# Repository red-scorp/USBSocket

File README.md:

# USBSocket project

USB Socket board came into existence as alternative to cheap miniUSB adapters which we not good enough for me.
These cheap boards do not care about D+/D- traced being equally long which is essential for USB wiring.
I had to design my own microUSB adapter board to fit my needs.

Following types of boards are available:

- **Type1** is breadboard friendly **microUSB** socket
- **Type2** is cable mount friendly **microUSB** socket
- **Type3** is breadboard friendly **miniUSB** socket
- **Type4** is cable mount friendly **miniUSB** socket
- **Type5** is breadboard friendly **USB** socket
- **Type6** is cable mount friendly **USB** socket
- **Type7** is breadboard friendly **PCB-USB** socket
- **Type8** is cable mount friendly **PCB-USB** socket
- **Type9** is breadboard friendly **USB Type-C** socket
- **Type10** is cable mount friendly **USB Type-C** socket

## USBSocket_Type1_v1.0

**USBSocket_Type1_v1.0** is a simple microUSB adapter board, which mostly designed to be breadboard friendly.

Preview:

[Schematics in PDF format](doc/USBSocket_Type1_v1.0.pdf)

Features:

- 2.54mm (0.1") raster breadboard friendly
- small size
- includes decoupling capacitor
- includes power LED indicator
- 3mm mount holes

CAM files are available.

## USBSocket_Type2_v1.0

**USBSocket_Type2_v1.0** is a simple microUSB adapter board mostly usable for smaller or cable applications.

Preview:

[Schematics in PDF format](doc/USBSocket_Type2_v1.0.pdf)

Features:

- 2.54mm (0.1") raster board friendly
- even smaller size
- suitable for cable mount
- shrink-tube friendly

CAM files are available.

## USBSocket_Type3_v1.0

**USBSocket_Type3_v1.0** is a simple miniUSB adapter board, which mostly designed to be breadboard friendly.

Preview:

[Schematics in PDF format](doc/USBSocket_Type3_v1.0.pdf)

Features:

- 2.54mm (0.1") raster breadboard friendly
- small size
- includes decoupling capacitor
- includes power LED indicator
- 3mm mount holes

CAM files are available.

## USBSocket_Type4_v1.0

**USBSocket_Type4_v1.0** is a simple miniUSB adapter board mostly usable for smaller or cable applications.

Preview:

[Schematics in PDF format](doc/USBSocket_Type4_v1.0.pdf)

Features:

- 2.54mm (0.1") raster board friendly
- even smaller size
- suitable for cable mount
- shrink-tube friendly

CAM files are available.

## USBSocket_Type5_v1.0

**USBSocket_Type5_v1.0** is a simple USB adapter board, which mostly designed to be breadboard friendly.

Preview:

[Schematics in PDF format](doc/USBSocket_Type5_v1.0.pdf)

Features:

- 2.54mm (0.1") raster breadboard friendly
- small size
- includes decoupling capacitor
- includes power LED indicator
- 3mm mount holes

CAM files are available.

## USBSocket_Type6_v1.0

**USBSocket_Type6_v1.0** is a simple USB adapter board mostly usable for smaller or cable applications.

Preview:

[Schematics in PDF format](doc/USBSocket_Type6_v1.0.pdf)

Features:

- 2.54mm (0.1") raster board friendly
- even smaller size
- suitable for cable mount
- shrink-tube friendly

CAM files are available.

## USBSocket_Type7_v1.0

**USBSocket_Type7_v1.0** is a simple PCB-USB adapter board, which mostly designed to be breadboard friendly.
This PCB board should be about 1.6-2.0mm thick!

Preview:

[Schematics in PDF format](doc/USBSocket_Type7_v1.0.pdf)

Features:

- 2.54mm (0.1") raster breadboard friendly
- small size
- includes decoupling capacitor
- includes power LED indicator
- 3mm mount holes

CAM files are available.

## USBSocket_Type8_v1.0

**USBSocket_Type8_v1.0** is a simple PCB-USB adapter board mostly usable for smaller or cable applications.
This PCB board should be about 1.6-2.0mm thick!

Preview:

[Schematics in PDF format](doc/USBSocket_Type8_v1.0.pdf)

Features:

- 2.54mm (0.1") raster board friendly
- even smaller size
- suitable for cable mount
- shrink-tube friendly

CAM files are available.

## USBSocket_Type9_v1.0

**USBSocket_Type9_v1.0** is a simple USB Type-C adapter board, which mostly designed to be breadboard friendly.

Preview:

[Schematics in PDF format](doc/USBSocket_Type9_v1.0.pdf)

Features:

- 2.54mm (0.1") raster breadboard friendly
- small size
- includes decoupling capacitor
- includes power LED indicator
- 3mm mount holes

CAM files are available.

## USBSocket_Type10_v1.0

**USBSocket_Type10_v1.0** is a simple USB Type-C adapter board mostly usable for smaller or cable applications.

Preview:

[Schematics in PDF format](doc/USBSocket_Type10_v1.0.pdf)

Features:

- 2.54mm (0.1") raster board friendly
- even smaller size
- suitable for cable mount
- shrink-tube friendly

CAM files are available.

## BOM

Bill Of Materials is currently available only for LCSC Electronic Components Distributor, which is probably cheapest anyway.

### LCSC BOM

|Designator  |Part/Value               |Package/Footprint    |LCSC #   |
|------------|-------------------------|---------------------|---------|
|CN1         |MOLEX 473460001          |SMD                  |C132560  |
|CN2         |MOLEX 675031230          |SMD                  |C136452  |
|CN3         |MOLEX 670688000          |TH                   |C114097  |
|CN4         |Hanbo Electronic MC-107S |SMD                  |C2874570 |
|C1\*        |Cap. 47uF                |0805                 |C109461  |
|C2\*        |Cap. 100nF               |0402                 |C60474   |
|LED1\*      |LED Green                |0603                 |C364559  |
|R1\*        |Res. 1K                  |0402                 |C384390  |
|R2\*        |Res. 56K                 |0402                 |C25796   |

\*) These passive components are optional but it's recommended to install them.

## How to help

Your contributions as code, resources, or finances are welcome! Please contact me directly via email at andriy.golovnya@gmail.com or through my [GitHub profile](https://github.com/red-scorp).

If you'd like to make a financial contribution, you can donate via [PayPal](http://paypal.me/redscorp) or [Ko-Fi](http://ko-fi.com/redscorp). Your support is greatly appreciated.

Thanks in advance!

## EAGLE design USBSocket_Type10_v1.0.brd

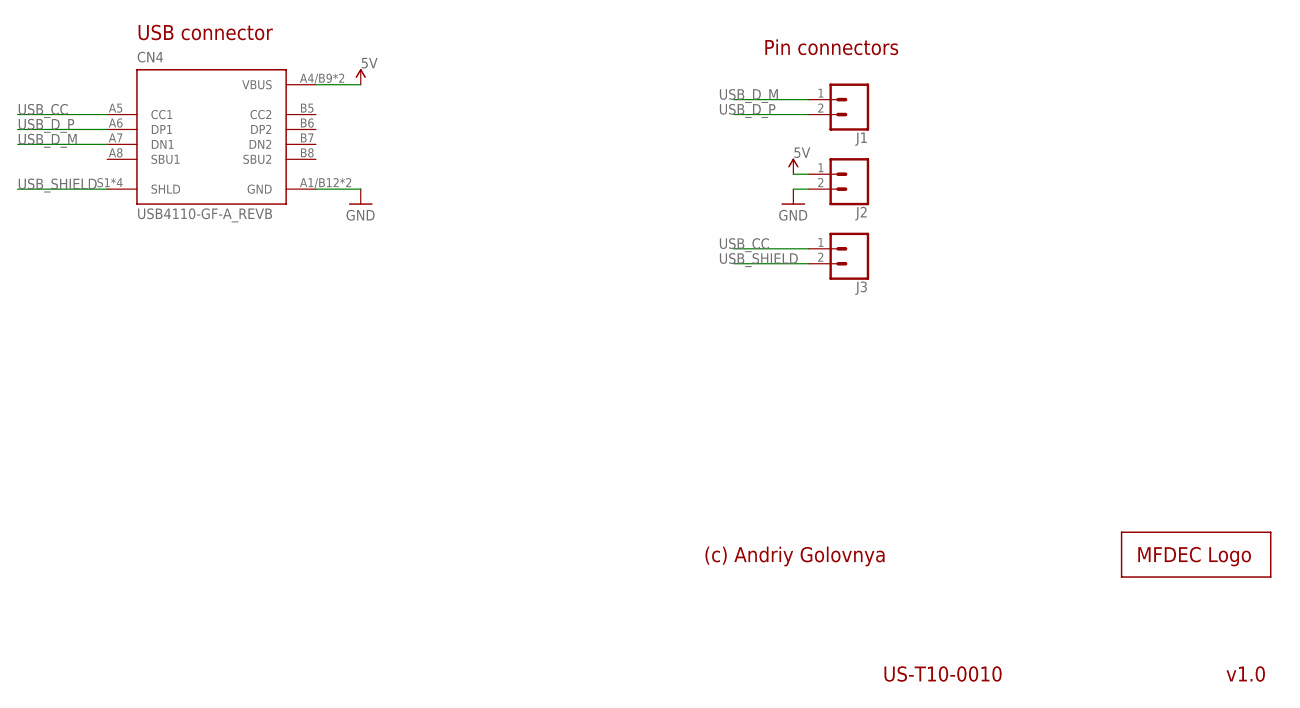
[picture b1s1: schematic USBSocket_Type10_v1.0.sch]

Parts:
CN4: USB4110-GF-A_REVB; GCT_USB4110-GF-A_REVB
J1, J2, J3: CONN_02; 1X02
LOGO1: MFDECLOGO_L_10MM; MFDEC_L_10MM

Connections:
5V: CN4.A4/B9 (VBUS), CN4.B4/A9 (VBUS), J2.1
GND: CN4.A1/B12 (GND), CN4.B1/A12 (GND), J2.2
USB_CC: CN4.A5 (CC1), J3.1
USB_D_M: CN4.A7 (DN1), J1.1
USB_D_P: CN4.A6 (DP1), J1.2
USB_SHIELD: CN4.S1 (SHLD), CN4.S2 (SHLD), CN4.S3 (SHLD), CN4.S4 (SHLD), J3.2

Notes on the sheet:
USB connector
v1.0
(c) Andriy Golovnya
US-T10-0010
Pin connectors

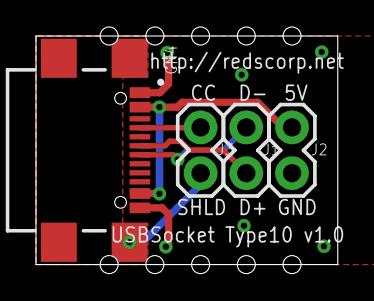
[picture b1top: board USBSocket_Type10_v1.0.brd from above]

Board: 2 copper layers, 16.8 x 12.7 mm, 5 parts (1 on the bottom side), 6 nets.

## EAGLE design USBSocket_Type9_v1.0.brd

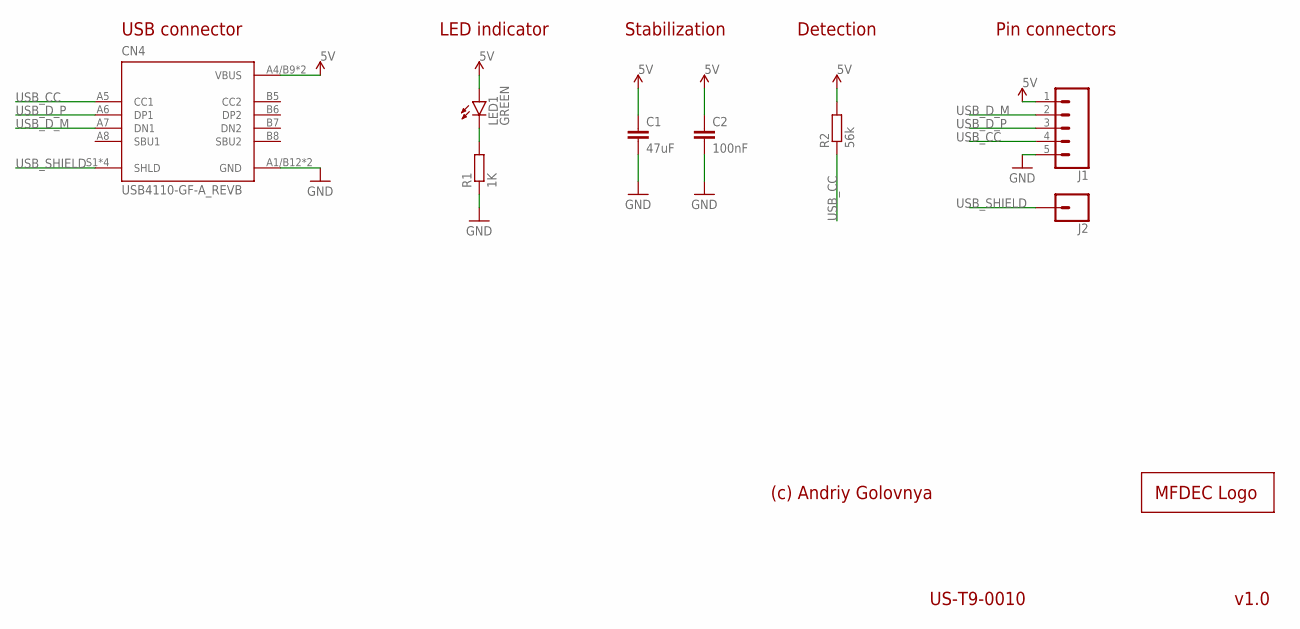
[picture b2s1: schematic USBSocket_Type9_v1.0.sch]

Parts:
C1: 47uF; C0805
C2: 100nF; C0402
CN4: USB4110-GF-A_REVB; GCT_USB4110-GF-A_REVB
J1: CONN_05PTH; 1X05
J2: CONN_01; 1X01
LED1: GREEN; SML0603
LOGO1: MFDECLOGO_L_10MM; MFDEC_L_10MM
R1: 1K; R0402
R2: 56k; R0402

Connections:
5V: C1.1, C2.1, CN4.A4/B9 (VBUS), CN4.B4/A9 (VBUS), J1.1, LED1.A, R2.2
GND: C1.2, C2.2, CN4.A1/B12 (GND), CN4.B1/A12 (GND), J1.5, R1.1
unnamed: LED1.C, R1.2
USB_CC: CN4.A5 (CC1), J1.4, R2.1
USB_D_M: CN4.A7 (DN1), J1.2
USB_D_P: CN4.A6 (DP1), J1.3
USB_SHIELD: CN4.S1 (SHLD), CN4.S2 (SHLD), CN4.S3 (SHLD), CN4.S4 (SHLD), J2.1

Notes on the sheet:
USB connector
v1.0
LED indicator
(c) Andriy Golovnya
US-T9-0010
Stabilization
Pin connectors
Detection

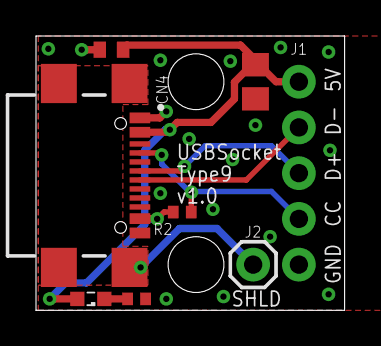
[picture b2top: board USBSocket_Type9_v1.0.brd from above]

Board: 2 copper layers, 17.1 x 15.2 mm, 9 parts (1 on the bottom side), 7 nets.

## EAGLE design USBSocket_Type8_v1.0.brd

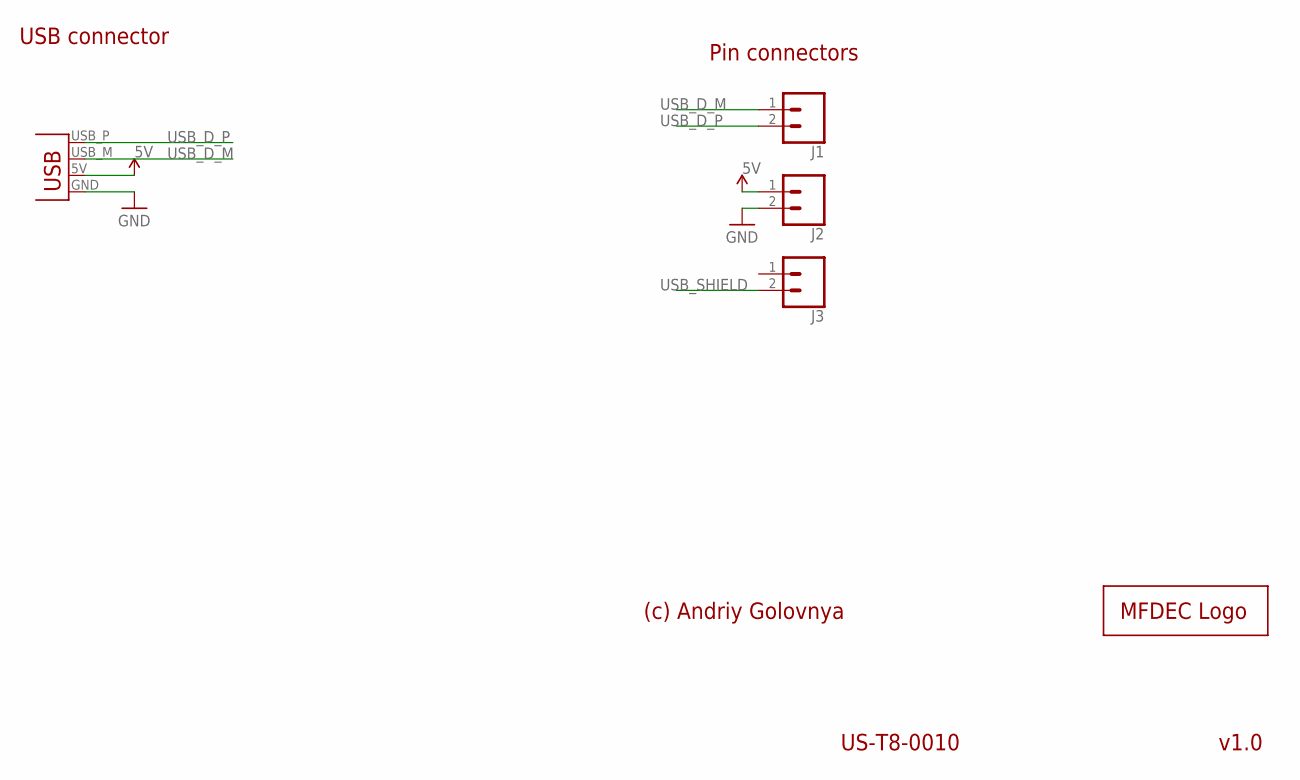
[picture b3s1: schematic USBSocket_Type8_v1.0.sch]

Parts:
J1, J2, J3: CONN_02; 1X02
LOGO1: MFDECLOGO_L_10MM; MFDEC_L_10MM
X1: USBPCB; USB-A-PCB

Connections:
5V: J2.1, X1.5V (VBUS)
GND: J2.2, X1.GND
USB_D_M: J1.1, X1.USB_M (D-)
USB_D_P: J1.2, X1.USB_P (D+)
USB_SHIELD: J3.2

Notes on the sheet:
USB connector
v1.0
(c) Andriy Golovnya
US-T8-0010
Pin connectors

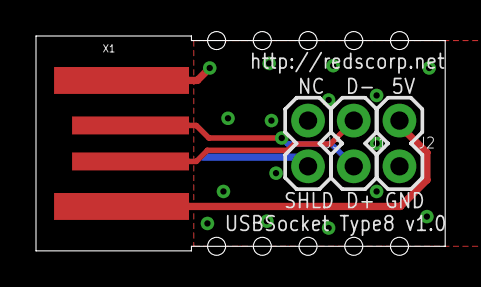
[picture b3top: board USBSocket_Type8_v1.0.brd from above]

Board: 2 copper layers, 22.7 x 11.9 mm, 5 parts (1 on the bottom side), 4 nets.

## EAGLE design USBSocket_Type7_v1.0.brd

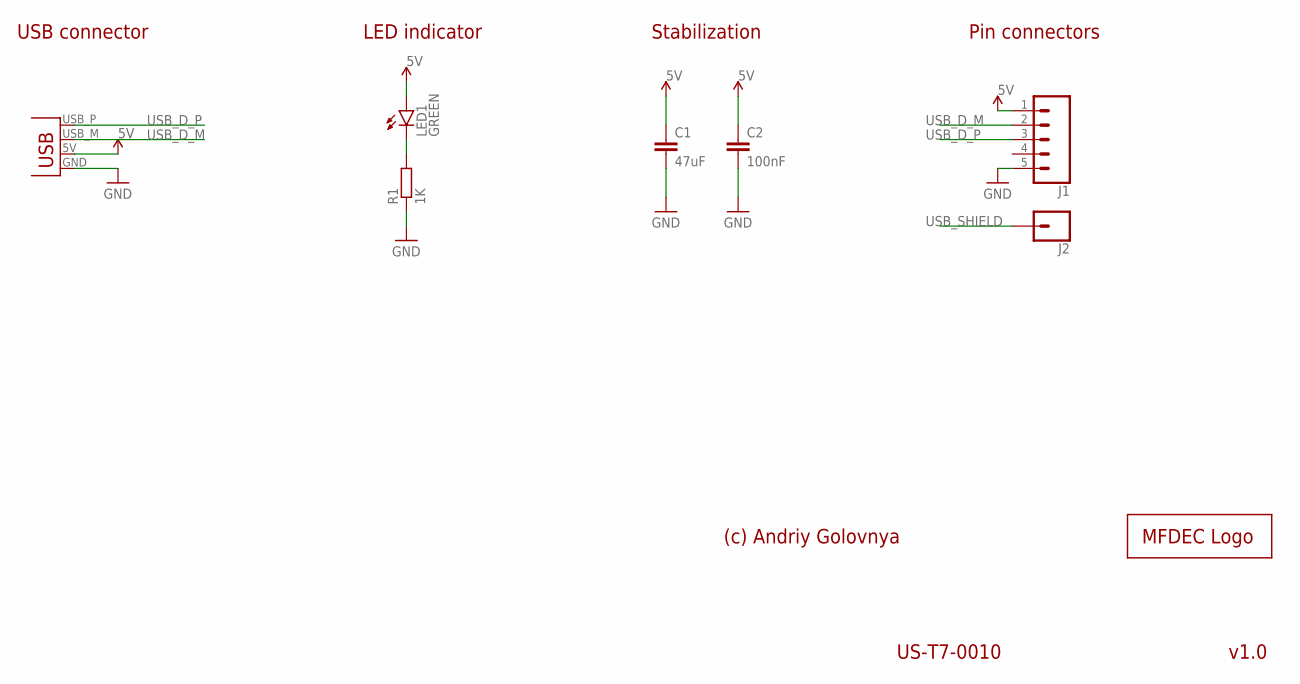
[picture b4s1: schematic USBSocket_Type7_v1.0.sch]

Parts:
C1: 47uF; C0805
C2: 100nF; C0402
J1: CONN_05PTH; 1X05
J2: CONN_01; 1X01
LED1: GREEN; SML0603
LOGO1: MFDECLOGO_L_10MM; MFDEC_L_10MM
R1: 1K; R0402
X1: USBPCB; USB-A-PCB

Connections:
5V: C1.1, C2.1, J1.1, LED1.A, X1.5V (VBUS)
GND: C1.2, C2.2, J1.5, R1.1, X1.GND
unnamed: LED1.C, R1.2
USB_D_M: J1.2, X1.USB_M (D-)
USB_D_P: J1.3, X1.USB_P (D+)
USB_SHIELD: J2.1

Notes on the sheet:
USB connector
v1.0
LED indicator
(c) Andriy Golovnya
US-T7-0010
Stabilization
Pin connectors

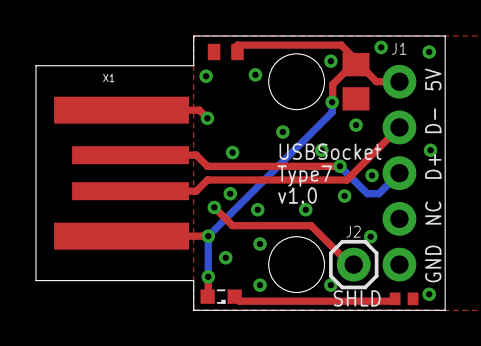
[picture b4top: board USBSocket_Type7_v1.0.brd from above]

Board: 2 copper layers, 22.7 x 15.2 mm, 8 parts (1 on the bottom side), 5 nets.

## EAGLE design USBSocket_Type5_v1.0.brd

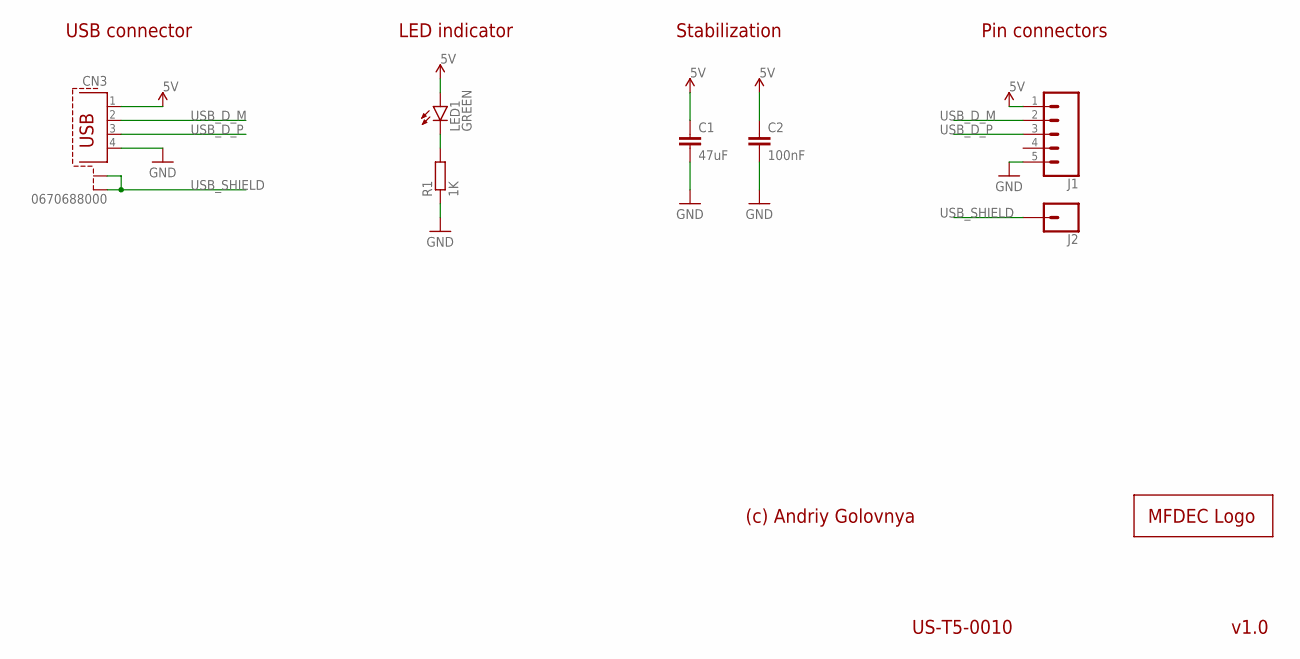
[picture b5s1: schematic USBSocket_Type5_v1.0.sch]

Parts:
C1: 47uF; C0805
C2: 100nF; C0402
CN3: 0670688000; PN61729-S
J1: CONN_05PTH; 1X05
J2: CONN_01; 1X01
LED1: GREEN; SML0603
LOGO1: MFDECLOGO_L_10MM; MFDEC_L_10MM
R1: 1K; R0402

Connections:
5V: C1.1, C2.1, CN3.1, J1.1, LED1.A
GND: C1.2, C2.2, CN3.4, J1.5, R1.1
unnamed: LED1.C, R1.2
USB_D_M: CN3.2, J1.2
USB_D_P: CN3.3, J1.3
USB_SHIELD: CN3.S1, CN3.S2, J2.1

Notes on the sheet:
USB connector
v1.0
LED indicator
(c) Andriy Golovnya
US-T5-0010
Stabilization
Pin connectors

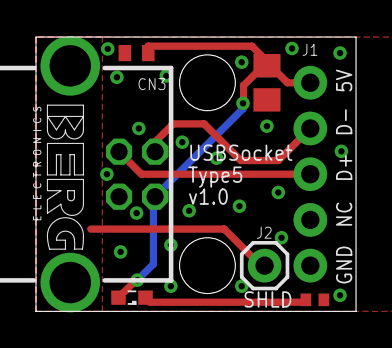
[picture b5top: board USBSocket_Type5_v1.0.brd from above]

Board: 2 copper layers, 17.8 x 15.2 mm, 8 parts (1 on the bottom side), 6 nets.

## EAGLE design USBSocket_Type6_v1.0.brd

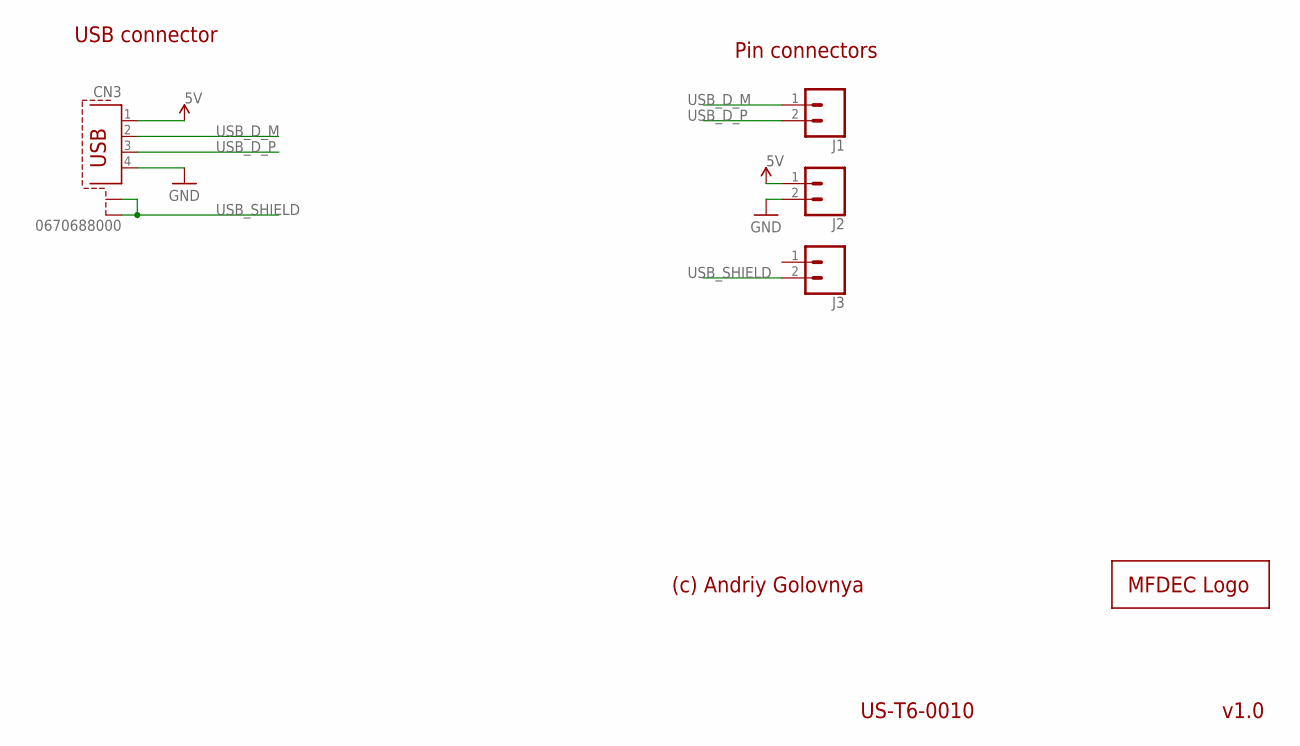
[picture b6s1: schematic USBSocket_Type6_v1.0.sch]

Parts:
CN3: 0670688000; PN61729-S
J1, J2, J3: CONN_02; 1X02
LOGO1: MFDECLOGO_L_10MM; MFDEC_L_10MM

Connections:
5V: CN3.1, J2.1
GND: CN3.4, J2.2
USB_D_M: CN3.2, J1.1
USB_D_P: CN3.3, J1.2
USB_SHIELD: CN3.S1, CN3.S2, J3.2

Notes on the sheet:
USB connector
v1.0
(c) Andriy Golovnya
US-T6-0010
Pin connectors

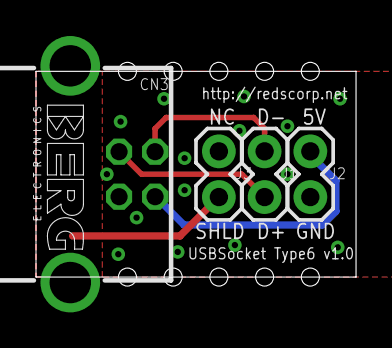
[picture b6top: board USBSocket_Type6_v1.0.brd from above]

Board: 2 copper layers, 17.8 x 11.4 mm, 5 parts (1 on the bottom side), 5 nets.

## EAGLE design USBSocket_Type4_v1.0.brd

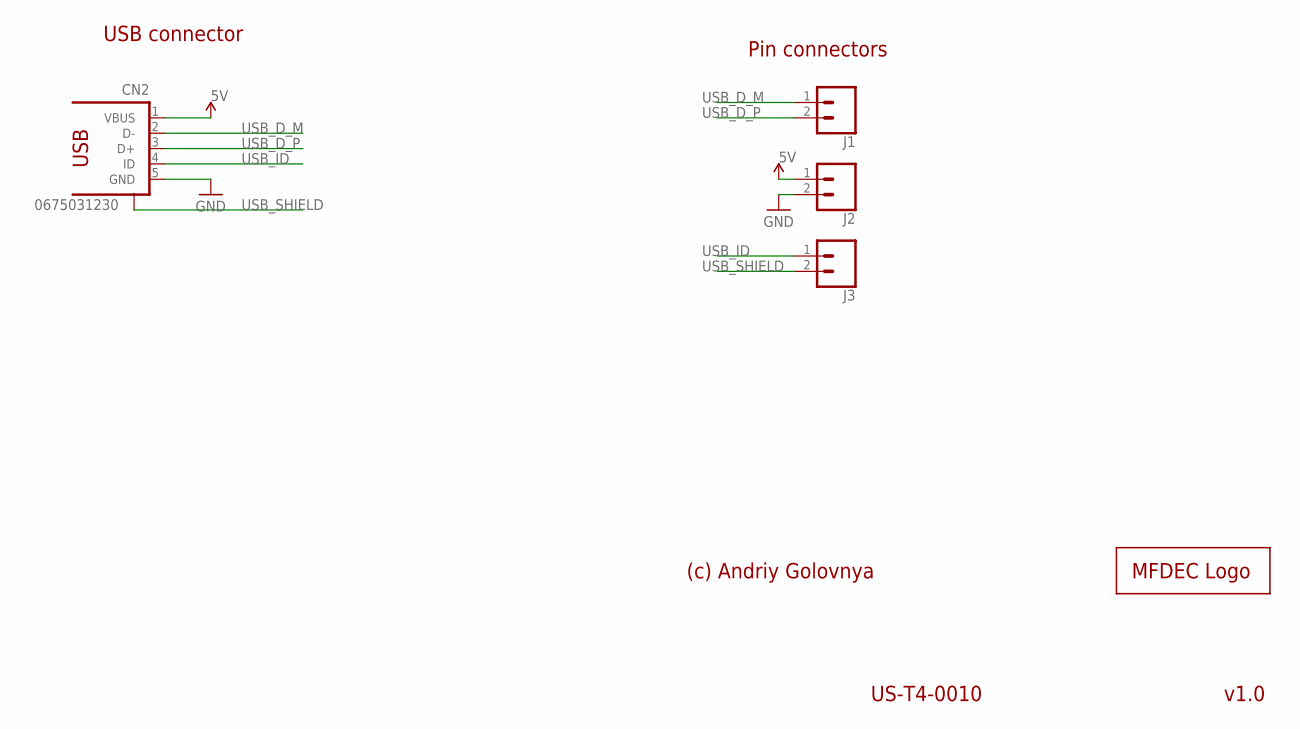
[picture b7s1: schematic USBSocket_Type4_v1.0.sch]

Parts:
CN2: 0675031230; PMX42_56579-0576
J1, J2, J3: CONN_02; 1X02
LOGO1: MFDECLOGO_L_10MM; MFDEC_L_10MM

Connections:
5V: CN2.1 (VBUS), J2.1
GND: CN2.5 (GND), J2.2
USB_D_M: CN2.2 (D-), J1.1
USB_D_P: CN2.3 (D+), J1.2
USB_ID: CN2.4 (ID), J3.1
USB_SHIELD: CN2.S1 (S), CN2.S2 (S), CN2.S3 (S), CN2.S4 (S), J3.2

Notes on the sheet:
USB connector
v1.0
(c) Andriy Golovnya
US-T4-0010
Pin connectors

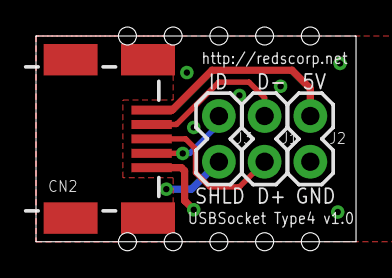
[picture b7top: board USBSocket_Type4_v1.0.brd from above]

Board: 2 copper layers, 17.8 x 11.4 mm, 5 parts (1 on the bottom side), 6 nets.

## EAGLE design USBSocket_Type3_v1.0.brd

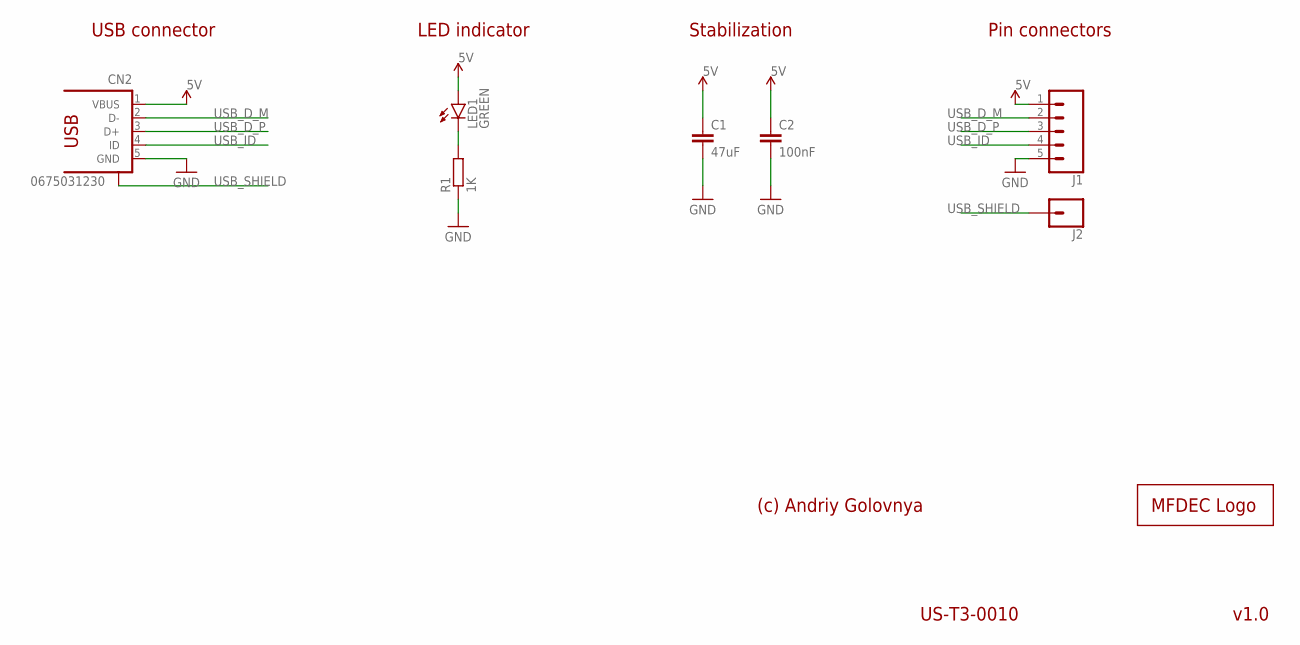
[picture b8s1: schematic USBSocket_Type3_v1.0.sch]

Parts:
C1: 47uF; C0805
C2: 100nF; C0402
CN2: 0675031230; PMX42_56579-0576
J1: CONN_05PTH; 1X05
J2: CONN_01; 1X01
LED1: GREEN; SML0603
LOGO1: MFDECLOGO_L_10MM; MFDEC_L_10MM
R1: 1K; R0402

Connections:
5V: C1.1, C2.1, CN2.1 (VBUS), J1.1, LED1.A
GND: C1.2, C2.2, CN2.5 (GND), J1.5, R1.1
unnamed: LED1.C, R1.2
USB_D_M: CN2.2 (D-), J1.2
USB_D_P: CN2.3 (D+), J1.3
USB_ID: CN2.4 (ID), J1.4
USB_SHIELD: CN2.S1 (S), CN2.S2 (S), CN2.S3 (S), CN2.S4 (S), J2.1

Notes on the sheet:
USB connector
v1.0
LED indicator
(c) Andriy Golovnya
US-T3-0010
Stabilization
Pin connectors

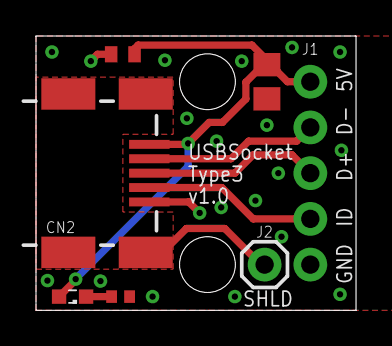
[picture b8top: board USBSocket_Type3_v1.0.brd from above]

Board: 2 copper layers, 17.8 x 15.2 mm, 8 parts (1 on the bottom side), 7 nets.

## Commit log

2021-02-28 Added Type1 USB socket board.
2021-02-28 Added Type2 board.
2021-02-28 Generated CAM for Type1 and Type2 boards. Generated PNG preview images. Generated PDF schematics.
2021-03-01 Add descriptions.
2021-03-01 Add funding file
2021-03-03 Fix DESCRIPTION.
2021-03-19 Approved ERC warnings.
2021-03-20 Added Type3-6 boards
2021-03-20 Added PDF schematics
2021-03-20 Added PNG previews
2021-03-20 Updated descriptions
2021-03-20 Added CAM files
2021-04-25 Fixed bottom silkscreen text.
2021-04-25 Added type7 board
2021-04-27 Fixed schematic and routing for t7 board.
2021-04-27 Added type8 board.
2021-04-27 Add PDF schematics and PNG preview for t7 and t8.
2021-04-27 Added CAM files for t7 and t8 boards.
2021-04-27 minor fixes.
2021-05-04 Update DESCRIPTION
2021-12-03 Fixed information about thickness of boards for type 7 and 8.
2021-12-05 cleanup.
2022-01-24 Added type9 board.
2022-01-24 Generated CAM files
2022-01-24 Generated PDF schematics. Generated PNG preview.
2022-01-25 Moved few stuff around on type 9 board. Generated CAM files. Generated PNG preview.
2022-01-25 Made type 9 board a bit shorter. Generated CAM files. Generated PNG preview.
2022-01-27 Added type10 board.
2023-08-28 Updated 'How to help' section.

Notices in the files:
parts and their libraries:
SparkFun-Connectors: Licensing: Creative Commons ShareAlike 4.0 International - https://creativecommons.org/licenses/by-sa/4.0
SparkFun: Licensing: CC v3.0 Share-Alike You are welcome to use this library for commercial purposes.
